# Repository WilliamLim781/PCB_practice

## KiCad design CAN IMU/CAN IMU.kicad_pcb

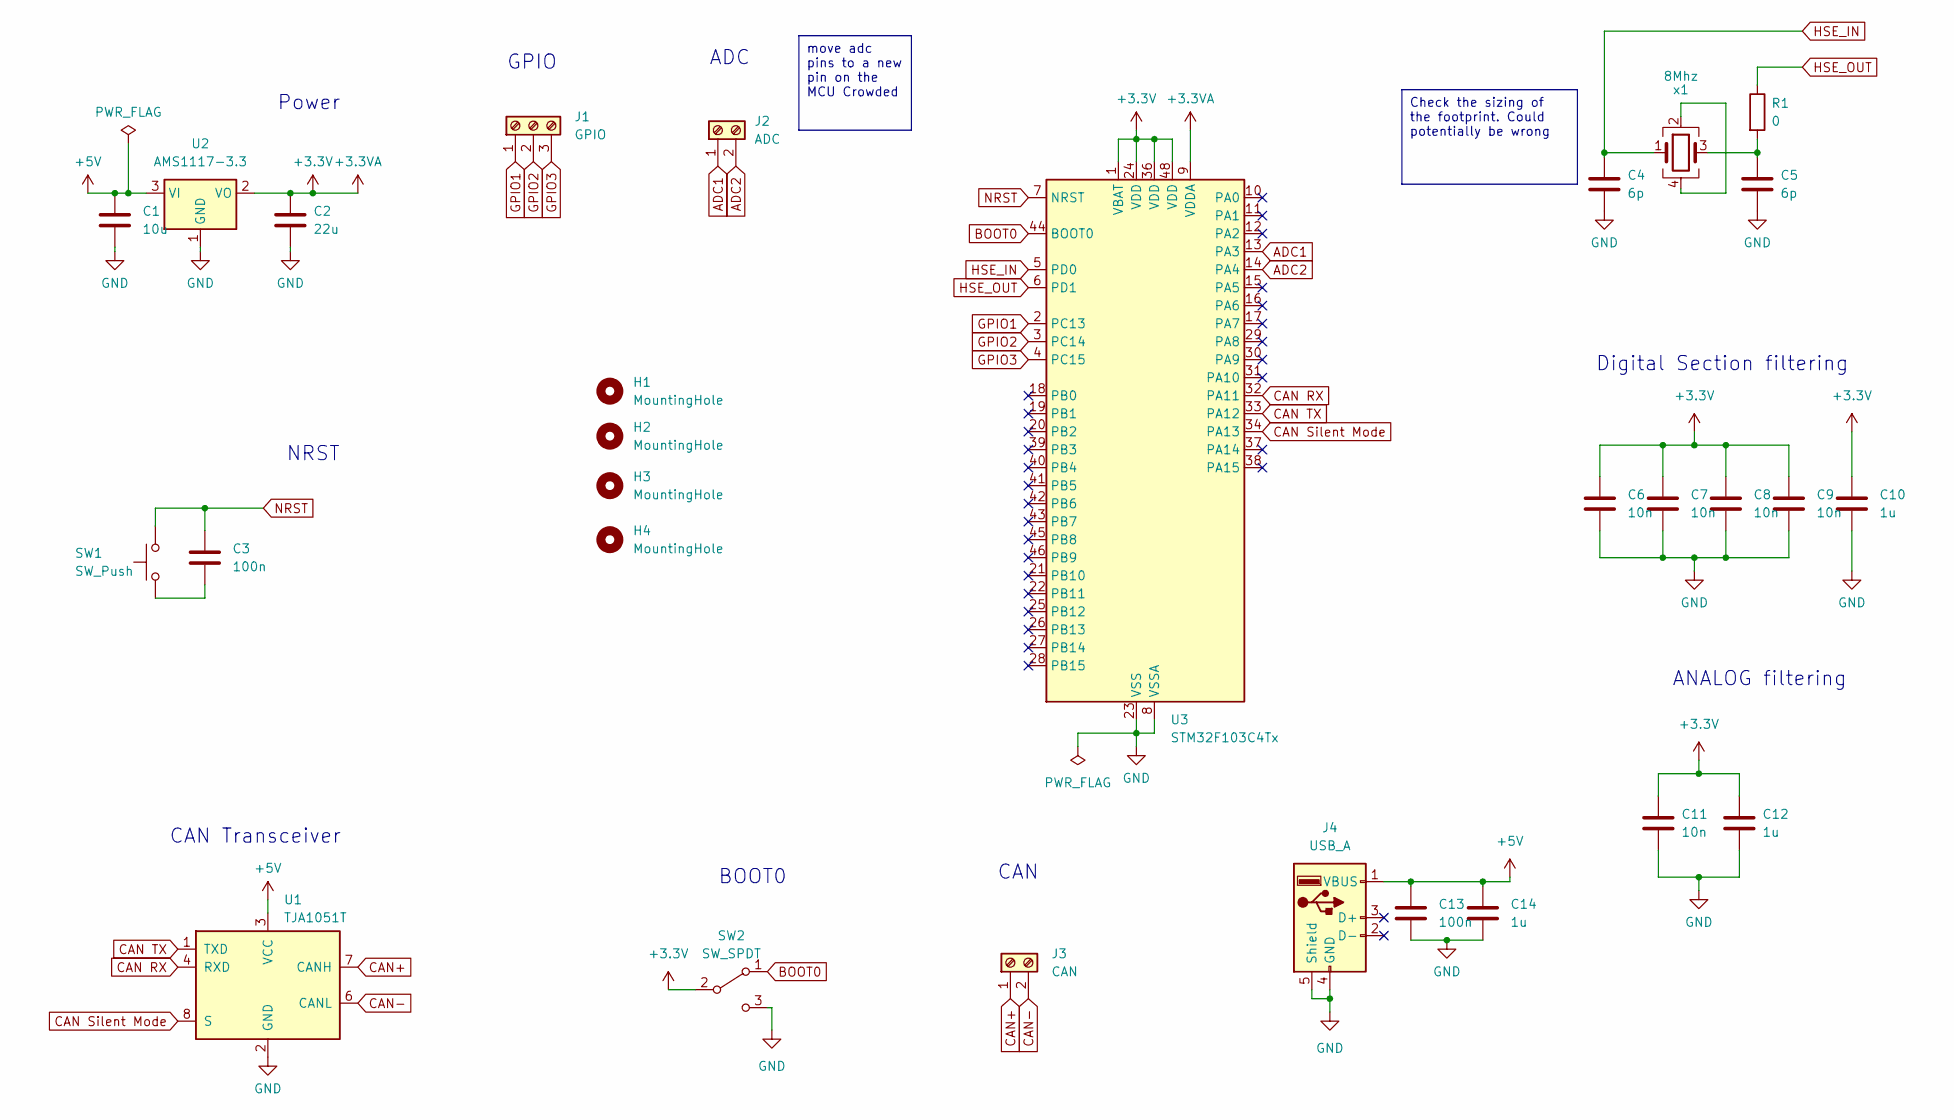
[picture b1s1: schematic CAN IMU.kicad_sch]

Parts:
C1: 10u; C_0603_1608Metric_Pad1.08x0.95mm_HandSolder
C2: 22u; C_0603_1608Metric_Pad1.08x0.95mm_HandSolder
C3, C13: 100n; C_0603_1608Metric_Pad1.08x0.95mm_HandSolder
C4, C5: 6p; C_0603_1608Metric_Pad1.08x0.95mm_HandSolder
C6, C7, C8, C9, C11: 10n; C_0603_1608Metric_Pad1.08x0.95mm_HandSolder
C10, C12, C14: 1u; C_0603_1608Metric_Pad1.08x0.95mm_HandSolder
H1, H2, H3, H4: MountingHole; MountingHole_4.3mm_M4_Pad
J1: GPIO; TerminalBlock_Phoenix_MKDS-1,5-3-5.08_1x03_P5.08mm_Horizont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
J2: ADC; TerminalBlock_Phoenix_MKDS-1,5-2_1x02_P5.00mm_Horizontal
J3: CAN; TerminalBlock_Phoenix_MKDS-1,5-2_1x02_P5.00mm_Horizontal
J4: USB_A; USB_A_Molex_67643_Horizontal
R1: 0; R_0603_1608Metric_Pad0.98x0.95mm_HandSolder
SW1: SW_Push; SW_SPST_PTS645
SW2: SW_SPDT; SW_SPDT_PCM12
U1: TJA1051T; SOIC-8_3.9x4.9mm_P1.27mm
U2: AMS1117-3.3; SOT-223-3_TabPin2
U3: STM32F103C4Tx; LQFP-48_7x7mm_P0.5mm
x1: 8Mhz; Oscillator_SMD_Abracon_ASE-4Pin_3.2x2.5mm_HandSoldering

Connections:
+3.3V: C2.1, C6.1, C7.1, C8.1, C9.1, C10.1, C11.1, C12.1, SW2.2 (B), U2.2 (VO), U3.1 (VBAT), U3.9 (VDDA), U3.24 (VDD), U3.36 (VDD), U3.48 (VDD)
+5V: C1.1, C13.1, C14.1, J4.1 (VBUS), U1.3 (VCC), U2.3 (VI)
ADC1: J2.1, U3.13 (PA3)
ADC2: J2.2, U3.14 (PA4)
BOOT0: SW2.1 (A), U3.44 (BOOT0)
CAN RX: U1.4 (RXD), U3.32 (PA11)
CAN Silent Mode: U1.8 (S), U3.34 (PA13)
CAN TX: U1.1 (TXD), U3.33 (PA12)
CAN+: J3.1, U1.7 (CANH)
CAN-: J3.2, U1.6 (CANL)
GND: C1.2, C2.2, C4.2, C5.2, C6.2, C7.2, C8.2, C9.2, C10.2, C11.2, C12.2, C13.2, C14.2, J4.4 (GND), J4.5 (Shield), SW2.3 (C), U1.2 (GND), U2.1 (GND), U3.8 (VSSA), U3.23 (VSS), U3.35 (VSS), U3.47 (VSS)
GPIO1: J1.1, U3.2 (PC13)
GPIO2: J1.2, U3.3 (PC14)
GPIO3: J1.3, U3.4 (PC15)
HSE_IN: C4.1, U3.5 (PD0), x1.1
HSE_OUT: R1.1, U3.6 (PD1)
NRST: C3.2, SW1.2, U3.7 (NRST)
unnamed: C3.1, SW1.1
unnamed: C5.1, R1.2, x1.3
unnamed: x1.2, x1.4

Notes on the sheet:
Check the sizing of the footprint. Could potentially be wrong
move adc pins to a new pin on the MCU Crowded
CAN Transceiver
Power
NRST
ANALOG filtering
GPIO
BOOT0
ADC
Digital Section filtering
CAN

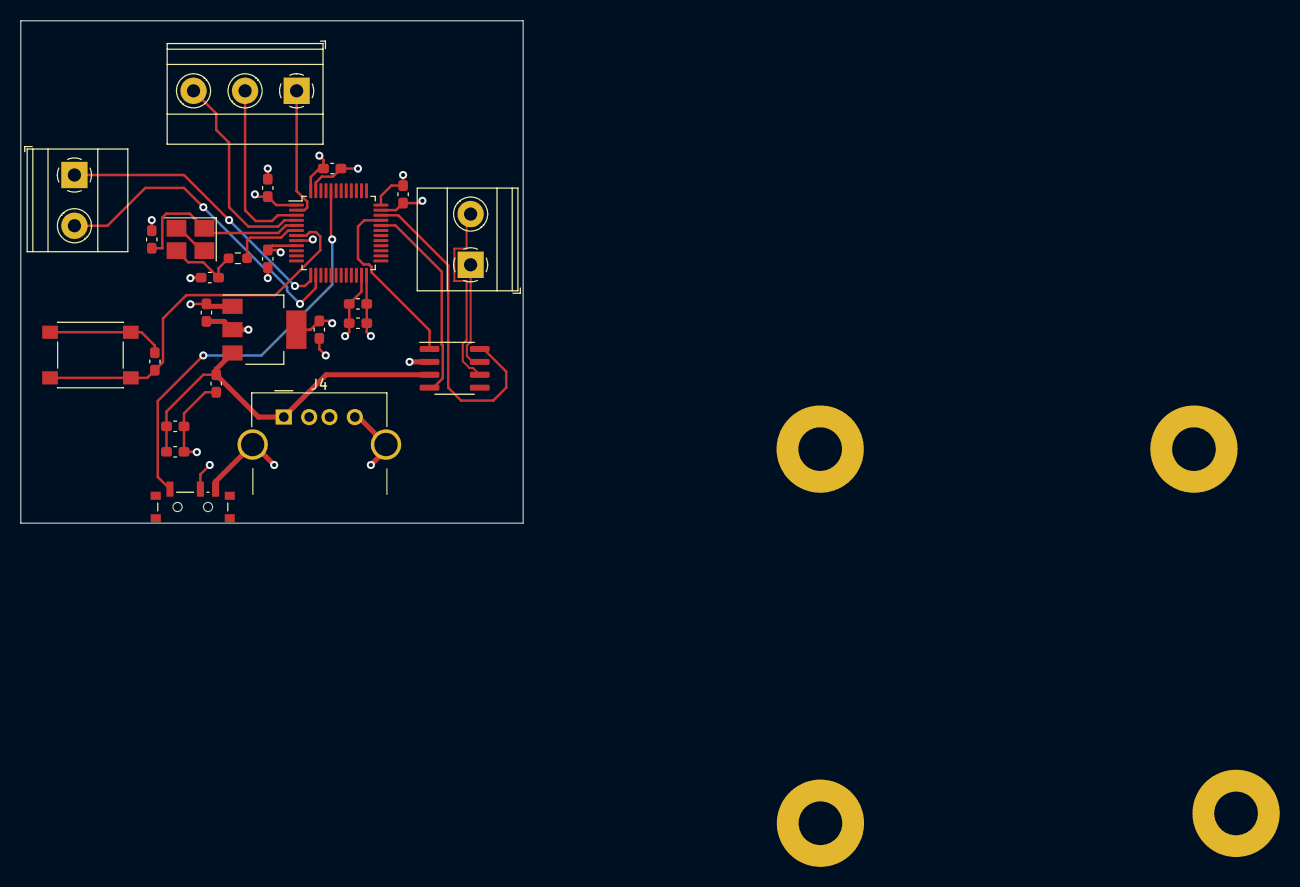
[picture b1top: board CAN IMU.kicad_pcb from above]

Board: 4 copper layers, 49.5 x 49.5 mm, 29 parts (0 on the bottom side), 20 nets.

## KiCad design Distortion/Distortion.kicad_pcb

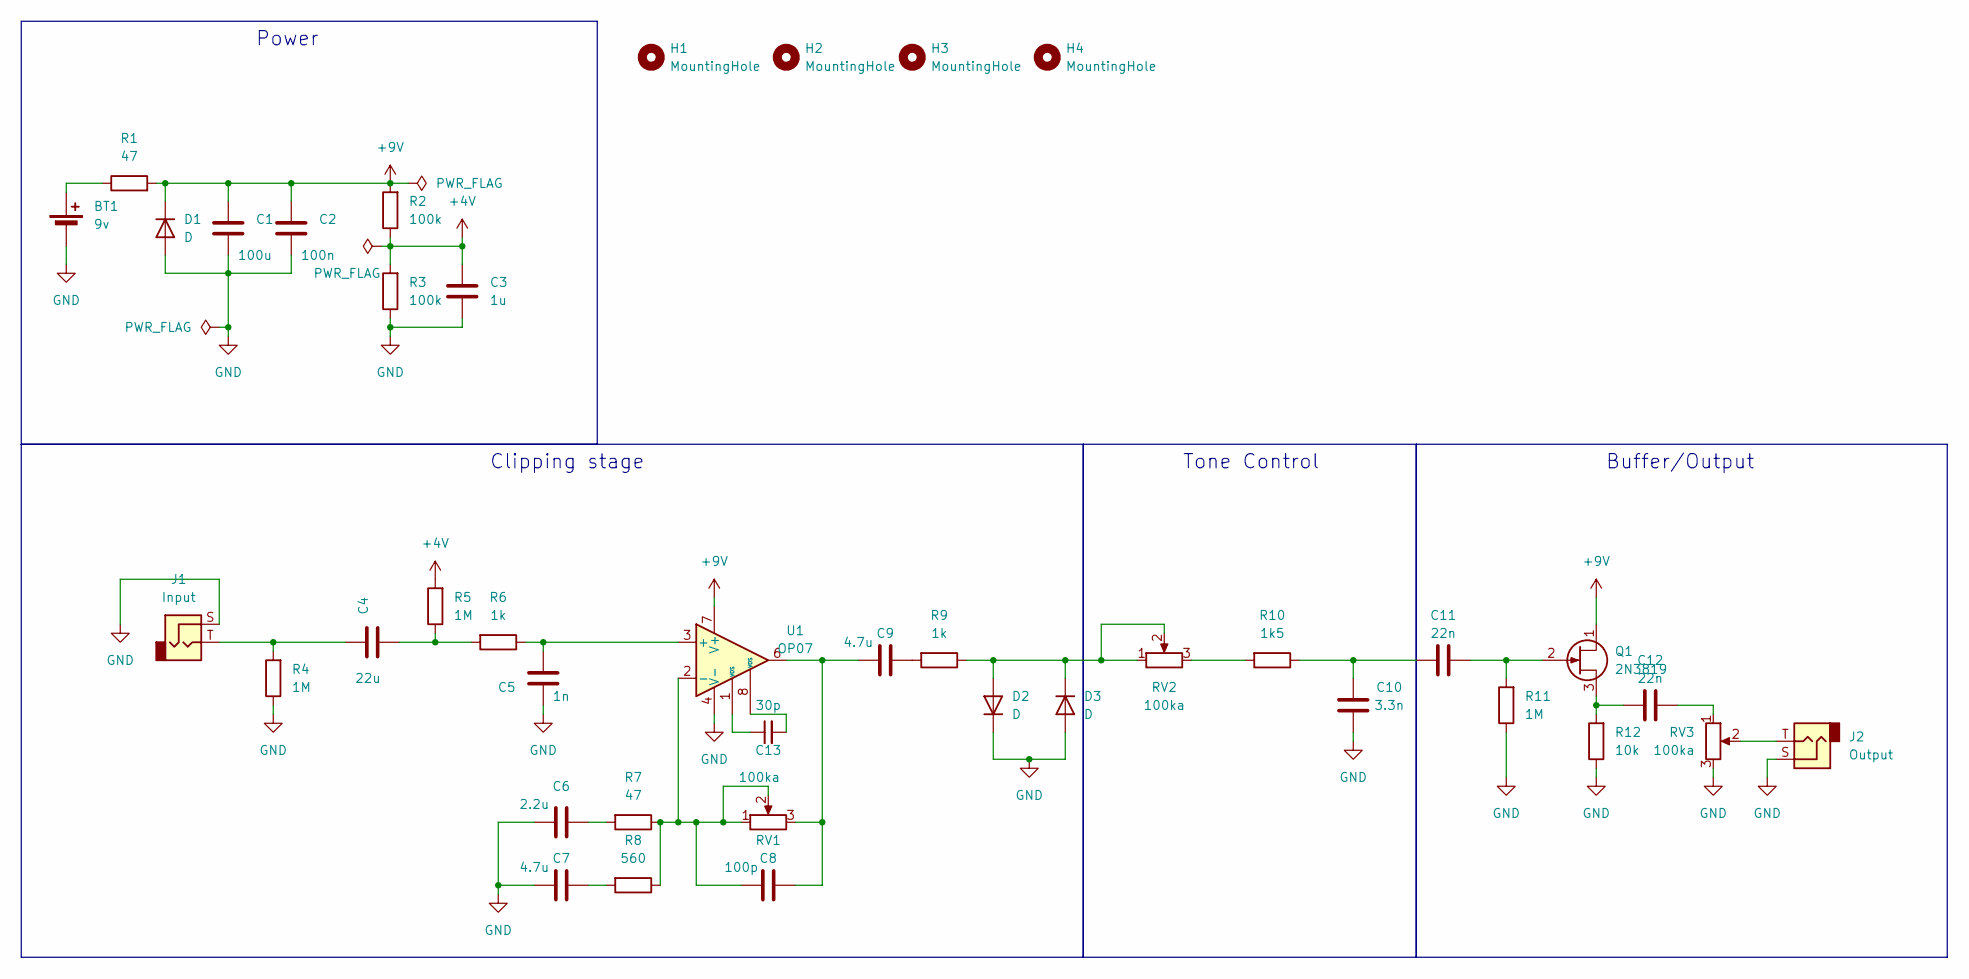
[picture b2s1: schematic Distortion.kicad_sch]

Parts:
BT1: 9v; BatteryHolder_Eagle_12BH611-GR
C1: 100u; C_Disc_D10.5mm_W5.0mm_P10.00mm
C2: 100n; C_Disc_D10.5mm_W5.0mm_P10.00mm
C3: 1u; C_Disc_D10.5mm_W5.0mm_P10.00mm
C4: 22u; C_Disc_D10.5mm_W5.0mm_P10.00mm
C5: 1n; C_Disc_D10.5mm_W5.0mm_P10.00mm
C6: 2.2u; C_Disc_D10.5mm_W5.0mm_P10.00mm
C7, C9: 4.7u; C_Disc_D10.5mm_W5.0mm_P10.00mm
C8: 100p; C_Disc_D10.5mm_W5.0mm_P10.00mm
C10: 3.3n; C_Disc_D10.5mm_W5.0mm_P10.00mm
C11, C12: 22n; C_Disc_D10.5mm_W5.0mm_P10.00mm
C13: 30p; C_Disc_D10.5mm_W5.0mm_P10.00mm
D1, D2, D3: D; D_DO-15_P12.70mm_Horizontal
H1, H2, H3, H4: MountingHole; MountingHole_3.5mm_Pad_Via
J1: Input; Jack_6.35mm_Neutrik_NMJ4HHD2_Horizontal
J2: Output; Jack_6.35mm_Neutrik_NMJ4HHD2_Horizontal
Q1: 2N3819; TO-92
R1, R7: 47; R_Axial_DIN0207_L6.3mm_D2.5mm_P10.16mm_Horizontal
R2, R3: 100k; R_Axial_DIN0207_L6.3mm_D2.5mm_P10.16mm_Horizontal
R4, R5, R11: 1M; R_Axial_DIN0207_L6.3mm_D2.5mm_P10.16mm_Horizontal
R6, R9: 1k; R_Axial_DIN0207_L6.3mm_D2.5mm_P10.16mm_Horizontal
R8: 560; R_Axial_DIN0207_L6.3mm_D2.5mm_P10.16mm_Horizontal
R10: 1k5; R_Axial_DIN0207_L6.3mm_D2.5mm_P10.16mm_Horizontal
R12: 10k; R_Axial_DIN0207_L6.3mm_D2.5mm_P10.16mm_Horizontal
RV1, RV2, RV3: 100ka; Potentiometer_Alps_RK09K_Single_Vertical
U1: OP07; DIP-8_W7.62mm_LongPads

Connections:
+4V: C3.1, R2.1, R3.2, R5.2
+9V: C1.1, C2.1, D1.1 (K), Q1.1 (D), R1.2, R2.2, U1.7 (V+)
GND: BT1.2 (-), C1.2, C2.2, C3.2, C5.1, C6.1, C7.1, C10.1, D1.2 (A), D2.1 (K), D3.2 (A), J1.S, J2.S, R3.1, R4.1, R11.1, R12.1, RV3.3, U1.4 (V-)
unnamed: BT1.1 (+), R1.1
unnamed: C4.1, J1.T, R4.2
unnamed: C4.2, R5.1, R6.2
unnamed: C6.2, R7.2
unnamed: C7.2, R8.2
unnamed: C8.2, C9.1, RV1.3, U1.6
unnamed: C9.2, R9.2
unnamed: C10.2, C11.2, R10.1
unnamed: C12.1, RV3.1
unnamed: C13.1, U1.1 (VOS)
unnamed: C13.2, U1.8 (VOS)
unnamed: D2.2 (A), D3.1 (K), R9.1, RV2.1, RV2.2
unnamed: J2.T, RV3.2
unnamed: C11.1, Q1.2 (G), R11.2
unnamed: C12.2, Q1.3 (S), R12.2
unnamed: R10.2, RV2.3
unnamed: C5.2, R6.1, U1.3 (+)
unnamed: C8.1, R7.1, R8.1, RV1.1, RV1.2, U1.2 (-)

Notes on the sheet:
Power
Tone Control
Clipping stage
Buffer/Output

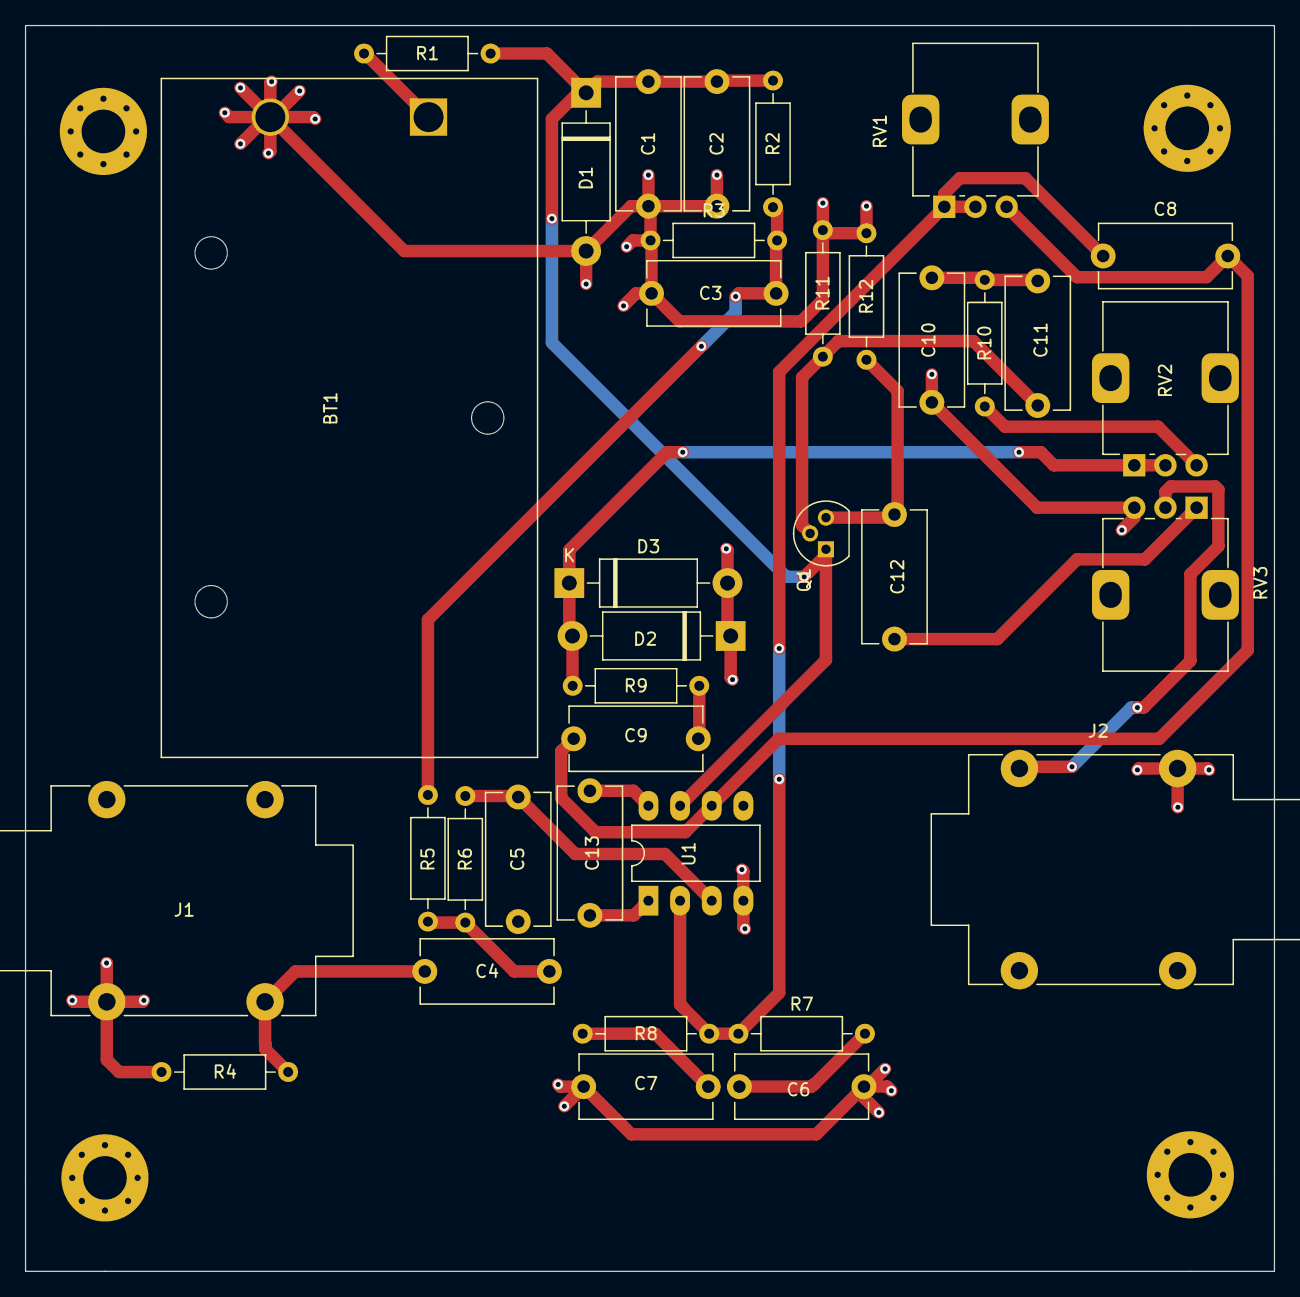
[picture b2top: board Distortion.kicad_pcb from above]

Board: 2 copper layers, 100.2 x 100.0 mm, 40 parts (0 on the bottom side), 21 nets.

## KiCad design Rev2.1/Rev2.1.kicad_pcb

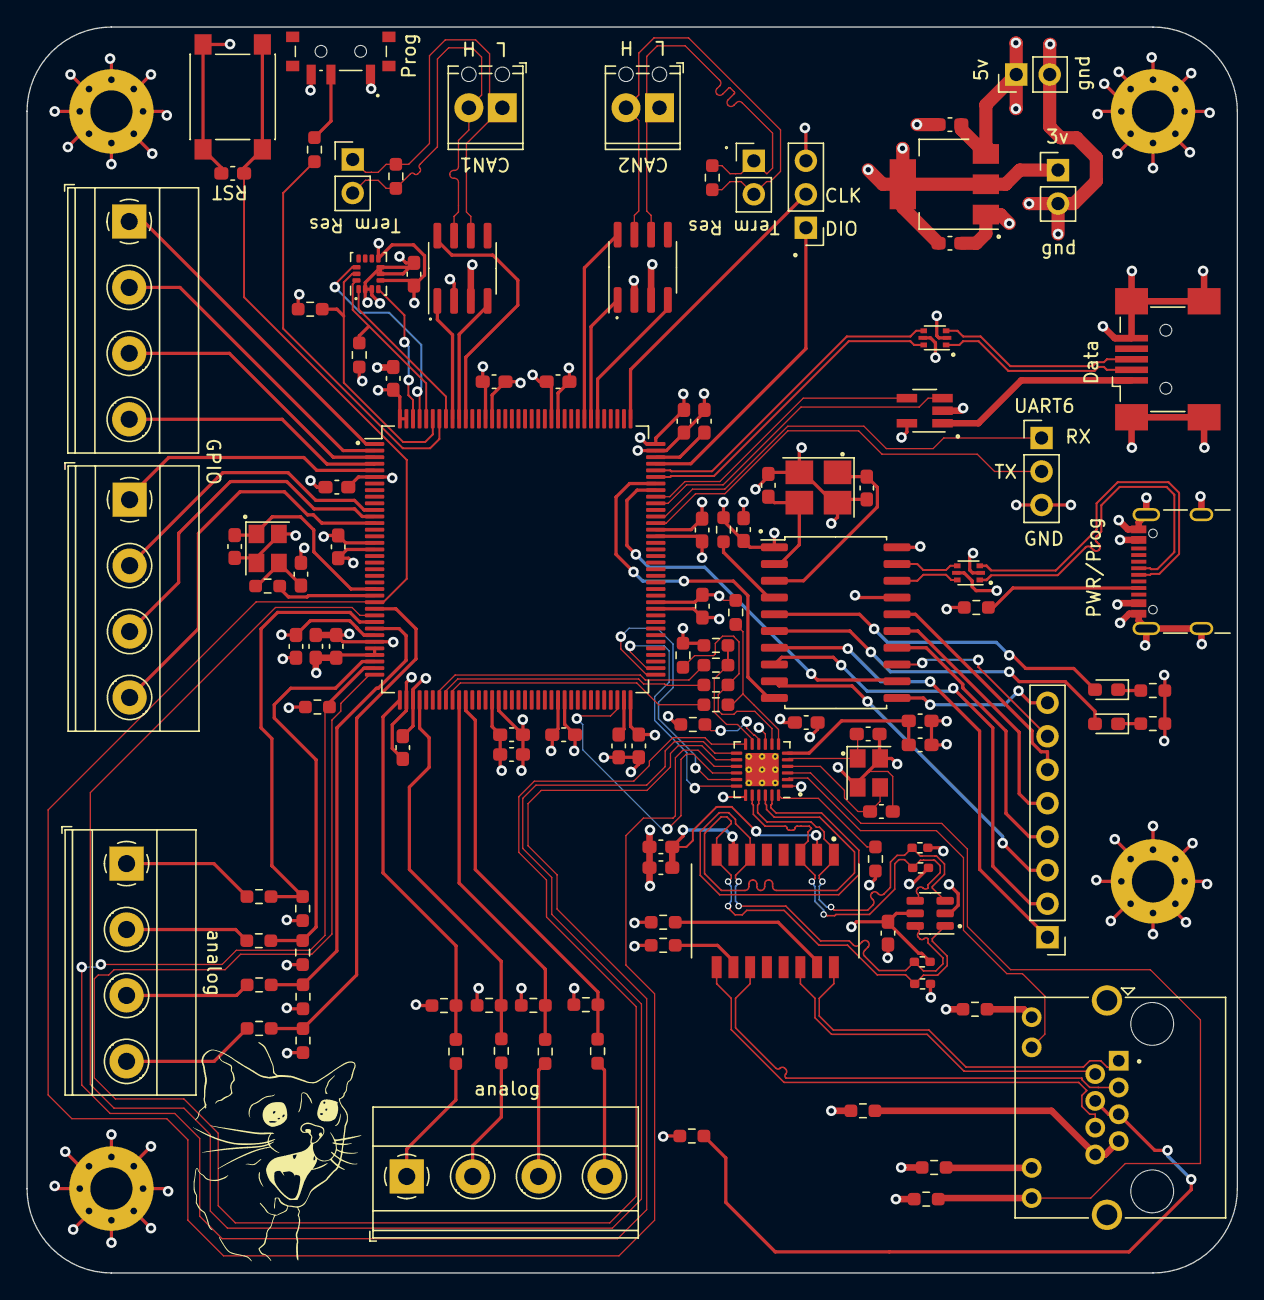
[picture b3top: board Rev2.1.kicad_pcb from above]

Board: 4 copper layers, 91.8 x 94.5 mm, 120 parts (0 on the bottom side), 117 nets.

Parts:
C1, C2, C5, C8, C11, C12, C23, C24, C25, C28, C33, C34, C35, C36, C37, C38, C39, C40, C41, C43, C45: 100n; C_0603_1608Metric_Pad1.08x0.95mm_HandSolder
C3, C4: 6p; C_0603_1608Metric_Pad1.08x0.95mm_HandSolder
C6: 470p; C_0603_1608Metric_Pad1.08x0.95mm_HandSolder
C7, C44: 1u; C_0603_1608Metric_Pad1.08x0.95mm_HandSolder
C9, C10: 22p; C_0603_1608Metric_Pad1.08x0.95mm_HandSolder
C26: 10u; C_0603_1608Metric_Pad1.08x0.95mm_HandSolder
C27, C31: 9p; C_0603_1608Metric_Pad1.08x0.95mm_HandSolder
C29, C30: 2.2u; C_0603_1608Metric_Pad1.08x0.95mm_HandSolder
C32: 22u; C_0603_1608Metric_Pad1.08x0.95mm_HandSolder
C42: 4.7u; C_0603_1608Metric_Pad1.08x0.95mm_HandSolder
D1, D2: LED; LED_0603_1608Metric_Pad1.05x0.95mm_HandSolder
H1, H2, H3, H4: MountingHole_Pad; MountingHole_3.2mm_M3_Pad_Via
J1, J3: Termination; PinHeader_1x02_P2.54mm_Vertical
J2: CAN2; TerminalBlock_Phoenix_MPT-0,5-2-2.54_1x02_P2.54mm_Horizontal
J4: CAN1; TerminalBlock_Phoenix_MPT-0,5-2-2.54_1x02_P2.54mm_Horizontal
J5: SWD; PinHeader_1x03_P2.54mm_Vertical
J6: USB_OTG; USB_Mini-B_Wuerth_65100516121_Horizontal
J7: GPIO1; TerminalBlock_Phoenix_MKDS-1,5-4_1x04_P5.00mm_Horizontal
J8: LIN Pots; TerminalBlock_Phoenix_MKDS-1,5-4_1x04_P5.00mm_Horizontal
J9: AIN; TerminalBlock_Phoenix_MKDS-1,5-4_1x04_P5.00mm_Horizontal
J10: Conn_01x08_Pin; PinHeader_1x08_P2.54mm_Vertical
J11: 3.3V power breakout; PinHeader_1x02_P2.54mm_Vertical
J12: 5V power breakout; PinHeader_1x02_P2.54mm_Vertical
J13: 8P8C_LED; RJ45_Amphenol_RJHSE538X
J14: GPIO2; TerminalBlock_Phoenix_MKDS-1,5-4_1x04_P5.00mm_Horizontal
J15: USART6; PinHeader_1x03_P2.54mm_Vertical
P2: USB_C_Plug_USB2.0; USB_C_Receptacle_GCT_USB4105-xx-A_16P_TopMnt_Horizontal
R1, R2: 120; R_0603_1608Metric_Pad0.98x0.95mm_HandSolder
R3, R9, R10, R11, R12, R13, R14, R15, R16, R36, R37, R39, R40, R41, R42: 10k; R_0603_1608Metric_Pad0.98x0.95mm_HandSolder
R4: 0; R_0603_1608Metric_Pad0.98x0.95mm_HandSolder
R5: 4k7; R_0603_1608Metric_Pad0.98x0.95mm_HandSolder
R6, R7, R45, R46: 2k2; R_0603_1608Metric_Pad0.98x0.95mm_HandSolder
R8: 5k1; R_0603_1608Metric_Pad0.98x0.95mm_HandSolder
R17, R18, R19, R20, R21, R22, R23, R24: 5k6; R_0603_1608Metric_Pad0.98x0.95mm_HandSolder
R25, R26, R27, R28: 75; R_0603_1608Metric_Pad0.98x0.95mm_HandSolder
R29, R30: 270; R_0603_1608Metric_Pad0.98x0.95mm_HandSolder
R31, R32, R33, R34: 50; R_0402_1005Metric_Pad0.72x0.64mm_HandSolder
R35: 12k1; R_0603_1608Metric_Pad0.98x0.95mm_HandSolder
R38, R43, R44: 33; R_0603_1608Metric_Pad0.98x0.95mm_HandSolder
SW3: SW_SPDT; SW_SPDT_PCM12
SW5: SW_Push; SW_SPST_PTS645
T1: H1102NLT; XFMR_H1102NLT
U1: STM32F429ZITx; LQFP-144_20x20mm_P0.5mm
U2, U4: TJA1051T; SOIC-8_3.9x4.9mm_P1.27mm
U3: AMS1117-3.3; SOT-223-3_TabPin2
U5: LGA-14_3x2.5mm_P0.5mm_LayoutBorder3x4y
U6, U10: USBLC6-2P6(ESD protection); SOT-666
U7: MCP2200T-I-SO; SOIC-20W_7.5x12.8mm_P1.27mm
U8: LAN8742A; VQFN-24-1EP_4x4mm_P0.5mm_EP2.5x2.5mm_ThermalVias
U9: STMPS2151STR(Current protection); SOT-23-5_HandSoldering
U12: USBLC6-4SC6; SOT-23-6
Y1: 12MHz; Crystal_SMD_3225-4Pin_3.2x2.5mm_HandSoldering
Y2: 16MHz; Crystal_SMD_3225-4Pin_3.2x2.5mm
Y3: 25Mhz; Crystal_SMD_3225-4Pin_3.2x2.5mm

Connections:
+3.3V: C1.1, C2.1, C5.1, C8.1, C23.1, C24.1, C25.1, C28.1, C32.1, C33.1, C34.1, C35.1, C36.1, C37.1, C38.1, C39.1, C40.1, C41.1, C42.1, C43.1, C44.1, J11.1, R5.2, R31.1, R32.1, R33.1, R34.1, R37.1, R39.1, R40.1, R41.1, R45.1, R46.1, SW3.1 (A), U1.6 (VBAT), U1.17 (VDD), U1.30 (VDD), U1.32 (VREF+), U1.33 (VDDA), U1.39 (VDD), U1.52 (VDD), U1.62 (VDD), U1.72 (VDD), U1.84 (VDD), U1.95 (VDD), U1.108 (VDD), U1.121 (VDD), U1.131 (VDD), U1.143 (PDR_ON), U1.144 (VDD), U3.2 (VO), U5.5 (VDDIO), U5.8 (VDD), U7.1 (VDD), U7.17 (V_USB), U8.1 (VDD2A), U8.9 (VDDIO), U8.19 (VDD1A), U12.5 (VBUS)
+5V: C26.1, J12.1, P2.A4 (VBUS), P2.A9 (VBUS), P2.B4 (VBUS), P2.B9 (VBUS), U2.3 (VCC), U3.3 (VI), U4.3 (VCC), U6.5 (VBUS), U9.5 (VIN), U10.5 (VBUS)
/CAN1+: J3.2, J4.2, R2.2, U4.7 (CANH)
/CAN1-: J3.1, J4.1, R2.1, U4.6 (CANL)
/CAN2+: J1.2, J2.2, R1.2, U2.7 (CANH)
/CAN2-: J1.1, J2.1, R1.1, U2.6 (CANL)
/Ethernet/RX+: R33.2, T1.6, U8.23 (RXP), U12.6 (I/O4)
/Ethernet/RX-: R34.2, T1.8, U8.22 (RXN), U12.1 (I/O1)
/Ethernet/RX->ESD+: J13.3, T1.11
/Ethernet/RX->ESD-: J13.6, T1.9
/Ethernet/TX+: R31.2, T1.1, U8.21 (TXP), U12.3 (I/O2)
/Ethernet/TX-: R32.2, T1.3, U8.20 (TXN), U12.4 (I/O3)
/Ethernet/TX->ESD+: J13.1, T1.16
/Ethernet/TX->ESD-: J13.2, T1.14
/USB wiring/USB->ESD+: P2.A6 (D+), U6.3 (I/O2)
/USB wiring/USB->ESD-: P2.A7 (D-), U6.1 (I/O1)
/USB wiring/VBUS1: J6.1 (VBUS), U9.1 (OUT)
A1: R12.2, R19.1, U1.26 (PC0)
A2: R9.2, R17.1, U1.28 (PC2)
A3: R11.2, R23.1, U1.29 (PC3)
A4: R10.2, R18.1, U1.34 (PA0)
BOOT0: R3.1, U1.138 (BOOT0)
CAN1_RX: U1.114 (PD0), U4.4 (RXD)
CAN1_TX: U1.115 (PD1), U4.1 (TXD)
CAN2_RX: U1.135 (PB5), U2.4 (RXD)
CAN2_TX: U1.136 (PB6), U2.1 (TXD)
CTS: J10.7, U7.13 (CTS)
ETH_CRS_DV: R38.1, U1.43 (PA7)
ETH_MDC: U1.27 (PC1), U8.13 (MDC)
ETH_MDIO: U1.36 (PA2), U8.12 (MDIO)
ETH_REF_CLK: R37.2, U1.35 (PA1), U8.14 (~INT/REFCLKO)
ETH_RXD0: R44.1, U1.44 (PC4)
ETH_RXD1: R43.2, U1.45 (PC5)
ETH_TXD0: U1.73 (PB12), U8.17 (TXD0)
ETH_TXD1: U1.74 (PB13), U8.18 (TXD1)
ETH_TX_EN: U1.70 (PB11), U8.16 (TXEN)
GND: C1.2, C2.2, C3.2, C4.2, C5.2, C6.1, C7.1, C8.2, C9.2, C10.2, C11.2, C12.2, C23.2, C24.2, C25.2, C26.2, C27.2, C28.2, C29.2, C30.2, C31.2, C32.2, C33.2, C34.2, C35.2, C36.2, C37.2, C38.2, C39.2, C40.2, C41.2, C42.2, C43.2, C44.2, C45.2, H1.1, H2.1, H3.1, H4.1, J5.3, J6.5 (GND), J6.6 (Shield), J11.2, J12.2, J15.3, P2.A1 (GND), P2.A12 (GND), P2.S1 (SHIELD), R6.1, R7.1, R8.2, R17.2, R18.2, R19.2, R20.2, R21.2, R22.2, R23.2, R24.2, R25.2, R26.2, R27.2, R28.2, R29.2, R30.2, R35.2, R36.2, R42.1, SW3.3 (C), SW5.1, U1.16 (VSS), U1.31 (VSSA), U1.38 (VSS), U1.51 (VSS), U1.61 (VSS), U1.83 (VSS), U1.94 (VSS), U1.107 (VSS), U1.120 (VSS), U1.130 (VSS), U2.2 (GND), U3.1 (GND), U4.2 (GND), U5.2 (SDX), U5.3 (SCX), U5.6 (GND), U5.7 (GND), U6.2 (GND), U7.20 (VSS), U8.25 (VSS), U9.2 (GND), U10.2 (GND), U12.2 (GND), Y1.2, Y1.4, Y2.2, Y2.4, Y3.2, Y3.4
GP0: J10.6, U7.16 (GP0/SSPND)
GP1: J10.5, U7.15 (GP1/USB-CFG)
GP2: J10.4, U7.14 (GP2)
GP3: J10.3, U7.9 (GP3)
GP4: J10.2, U7.8 (GP4)
GP5: J10.1, U7.7 (GP5)
GPIO1: J7.1, U1.1 (PE2)
GPIO2: J7.2, U1.2 (PE3)
GPIO3: J7.3, U1.3 (PE4)
GPIO4: J7.4, U1.4 (PE5)
GPIO5: J14.1, U1.5 (PE6)
GPIO6: J14.2, U1.11 (PF1)
GPIO7: J14.3, U1.12 (PF2)
GPIO8: J14.4, U1.13 (PF3)
HSE_IN: C27.1, U1.23 (PH0), Y2.1
HSE_OUT: R4.1, U1.24 (PH1)
INTSEL_LED: J13.10, U8.2 (LED2/~INTSEL)
L1: R13.2, R20.1, U1.37 (PA3)
L2: R14.2, R21.1, U1.40 (PA4)
L3: R15.2, R22.1, U1.46 (PB0)
L4: R16.2, R24.1, U1.47 (PB1)
LSM6DSOX_CS: U1.141 (PE0), U5.12 (CS)
LSM6DSOX_SCL: R45.2, U1.139 (PB8), U5.13 (SCL)
LSM6DSOX_SDA: R46.2, U1.140 (PB9), U5.14 (SDA)
LSM6DSOX_SDO: U1.137 (PB7), U5.1 (SD0)
LSM6DSOX_int1: U1.142 (PE1), U5.4 (INT1)
NRST: C45.1, SW5.2, U1.25 (NRST), U8.15 (~RST)
unnamed: C11.1, C12.1, T1.2, T1.7
unnamed: C31.1, R4.2, Y2.3
unnamed: D1.2 (A), U7.6 (GP6/RxLED)
unnamed: D1.1 (K), R6.2
unnamed: D2.2 (A), U7.5 (GP7/TxLED)
unnamed: D2.1 (K), R7.2
unnamed: J8.1, R9.1
unnamed: J8.2, R10.1
unnamed: J8.3, R11.1
unnamed: J8.4, R12.1
unnamed: J9.1, R13.1
unnamed: J9.2, R14.1
unnamed: J9.3, R15.1
unnamed: J9.4, R16.1
unnamed: J13.4, J13.5, R25.1
unnamed: J13.7, J13.8, R28.1
unnamed: J13.9, R29.1
unnamed: J13.11, R30.1
unnamed: P2.A5 (CC), R8.1
unnamed: R26.1, T1.15
unnamed: R27.1, T1.10
unnamed: R3.2, SW3.2 (B)
unnamed: C3.1, U7.2 (OSC1), Y1.3
unnamed: C4.1, U7.3 (OSC2), Y1.1
unnamed: R5.1, U7.4 (RST)
unnamed: R38.2, R41.2, U8.11 (CRS_DV/MODE2)
unnamed: R35.1, U8.24 (RBIAS)
unnamed: R39.2, R44.2, U8.8 (RXD0/MODE0)
unnamed: R40.2, R43.1, U8.7 (RXD1/MODE1)
unnamed: R42.2, U8.10 (RXER/PHYAD0)
unnamed: C6.2, C7.2, U8.6 (VDDCR)
unnamed: C9.1, U8.5 (XTAL1/CLKIN), Y3.1
unnamed: C10.1, U8.4 (XTAL2), Y3.3
REGOFF_LED: J13.12, R36.1, U8.3 (LED1/REGOFF)
RTS: J10.8, U7.11 (RTS)
STMPS2151STR_EN: U1.100 (PA8), U9.4 (EN)
STMPS2151STR_FAULT: U1.99 (PC9), U9.3 (FAULT)
SYS_JTCK_SWCLK: J5.2, U1.109 (PA14)
SYS_JTMS_SWDIO: J5.1, U1.105 (PA13)
Silent_Mode1: U1.116 (PD2), U4.8 (S)
Silent_Mode2: U1.134 (PB4), U2.8 (S)
USART1_RX: U1.102 (PA10), U7.10 (TX)
USART1_TX: U1.101 (PA9), U7.12 (RX)
USART6_RX: J15.1, U1.97 (PC7)
USART6_TX: J15.2, U1.96 (PC6)
USBData->ESD+: J6.3 (D+), U10.3 (I/O2)
USBData->ESD-: J6.2 (D-), U10.1 (I/O1)
USB_DATA+: U1.104 (PA12), U10.4 (I/O2)
USB_DATA-: U1.103 (PA11), U10.6 (I/O1)
USB_PROG+: U6.4 (I/O2), U7.19 (D+)
USB_PROG-: U6.6 (I/O1), U7.18 (D-)
VCAP_1: C29.1, U1.71 (VCAP_1)
VCAP_2: C30.1, U1.106 (VCAP_2)

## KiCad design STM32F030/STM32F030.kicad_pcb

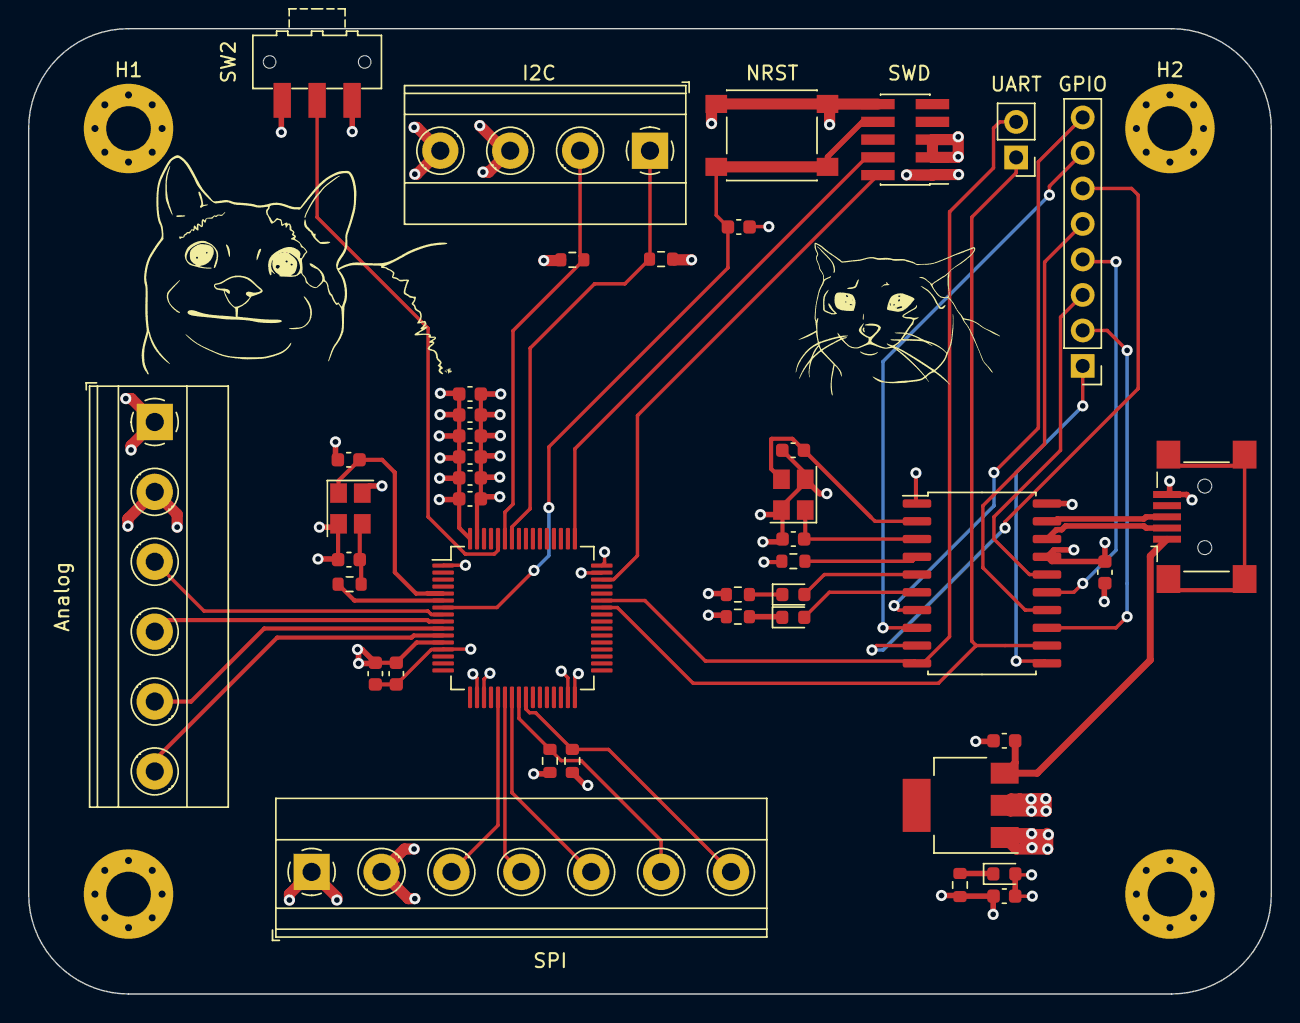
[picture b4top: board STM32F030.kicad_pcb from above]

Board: 4 copper layers, 88.9 x 69.1 mm, 46 parts (0 on the bottom side), 41 nets.

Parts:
Analog: analog pins; TerminalBlock_Phoenix_MKDS-1,5-6_1x06_P5.00mm_Horizontal
C1: 4.7u; C_0603_1608Metric
C2, C3, C4, C5, C6, C12: 100n; C_0603_1608Metric
C7: 10n; C_0603_1608Metric
C8: 1u; C_0603_1608Metric
C9: .1u; C_0603_1608Metric
C10, C11: 9p; C_0603_1608Metric
C13, C14: 6p; C_0603_1608Metric
C15: 10u; C_0603_1608Metric
C16: 22u; C_0603_1608Metric
D1, D2, D3: LED; LED_0603_1608Metric
GPIO: MCP2200 GPIO; PinHeader_1x08_P2.54mm_Vertical
H1, H2, H3, H4: MountingHole; MountingHole_3.2mm_M3_Pad_Via
I2C: I2C; TerminalBlock_Phoenix_MKDS-1,5-4_1x04_P5.00mm_Horizontal
J1: USB_OTG; USB_Mini-B_Lumberg_2486_01_Horizontal
NRST: NRST; SW_SPST_PTS645
R1: 47; R_0603_1608Metric
R2, R6: 10k; R_0603_1608Metric
R3, R4, R5, R7, R9: 2k2; R_0603_1608Metric
R8: 4k7; R_0603_1608Metric
SPI: SPI; TerminalBlock_Phoenix_MKDS-1,5-7_1x07_P5.00mm_Horizontal
SW2: BOOT0; SW_SPDT_CK-JS102011SAQN
SWD: SWD; PinHeader_2x05_P1.27mm_Vertical_SMD
U1: STM32F030RCTx; LQFP-64_10x10mm_P0.5mm
U2: MCP2200T-I-SO; SOIC-20W_7.5x12.8mm_P1.27mm
U3: AZ1117-3.3; SOT-223
UART: UART; PinHeader_1x02_P2.54mm_Vertical
Y1: 16MHz; Crystal_SMD_3225-4Pin_3.2x2.5mm
Y2: 12MHz; Crystal_SMD_3225-4Pin_3.2x2.5mm

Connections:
+3.3V: Analog.2, C1.1, C2.1, C3.1, C4.1, C5.1, C6.1, C7.1, C8.1, C12.1, C16.1, D3.2 (A), I2C.3, R2.1, R4.1, R5.1, R6.1, R8.2, SPI.2, SW2.1 (A), SWD.1, U1.1 (VDD), U1.13 (VDDA), U1.19 (VDD), U1.32 (VDD), U1.48 (VDD), U1.64 (VDD), U2.1 (VDD), U2.17 (V_USB), U3.2 (VO)
+5V: C15.1, J1.1 (VBUS), U3.3 (VI)
Boot0: SW2.2 (B), U1.60 (BOOT0)
CTS: GPIO.2, U2.13 (CTS)
GND: Analog.1, C1.2, C2.2, C3.2, C4.2, C5.2, C6.2, C7.2, C8.2, C9.2, C10.2, C11.2, C12.2, C13.2, C14.2, C15.2, C16.2, I2C.4, J1.5 (GND), NRST.1, R3.1, R7.1, R9.1, SPI.1, SW2.3 (C), SWD.3, SWD.5, SWD.10, U1.12 (VSSA), U1.18 (VSS), U1.31 (VSS), U1.47 (VSS), U1.63 (VSS), U2.20 (VSS), U3.1 (GND), Y1.2, Y1.4, Y2.2, Y2.4
GP0: GPIO.3, U2.16 (GP0/SSPND)
GP1: GPIO.4, U2.15 (GP1/USB-CFG)
GP2: GPIO.5, U2.14 (GP2)
GP3: GPIO.6, U2.9 (GP3)
GP4: GPIO.7, U2.8 (GP4)
GP5: GPIO.8, U2.7 (GP5)
HSE_IN: C10.1, U1.5 (PF0), Y1.1
HSE_OUT: R1.1, U1.6 (PF1)
I2C1_SCL: I2C.1, R4.2, U1.58 (PB6)
I2C1_SDA: I2C.2, R5.2, U1.59 (PB7)
Lin_Pots1: Analog.3, U1.8 (PC0)
Lin_Pots2: Analog.4, U1.9 (PC1)
Lin_Pots3: Analog.5, U1.10 (PC2)
Lin_Pots4: Analog.6, U1.11 (PC3)
NRST: C9.1, NRST.2, SWD.8, U1.7 (NRST)
unnamed: C11.1, R1.2, Y1.3
unnamed: D1.2 (A), U2.6 (GP6/RxLED)
unnamed: D1.1 (K), R3.2
unnamed: D2.2 (A), U2.5 (GP7/TxLED)
unnamed: D2.1 (K), R7.2
unnamed: D3.1 (K), R9.2
unnamed: C14.1, U2.2 (OSC1), Y2.3
unnamed: C13.1, U2.3 (OSC2), Y2.1
unnamed: R8.1, U2.4 (RST)
RTS: GPIO.1, U2.11 (RTS)
SPI1_CS1: R2.2, SPI.6, U1.24 (PC4)
SPI1_CS2: R6.2, SPI.7, U1.25 (PC5)
SPI1_MISO: SPI.4, U1.22 (PA6)
SPI1_MOSI: SPI.5, U1.23 (PA7)
SPI1_SCK: SPI.3, U1.21 (PA5)
SWCLK: SWD.4, U1.49 (PA14)
SWDIO: SWD.2, U1.46 (PA13)
USART1_RX: U1.43 (PA10), U2.10 (TX), UART.2
USART1_TX: U1.42 (PA9), U2.12 (RX), UART.1
USBD+: J1.3 (D+), U2.19 (D+)
USBD-: J1.2 (D-), U2.18 (D-)

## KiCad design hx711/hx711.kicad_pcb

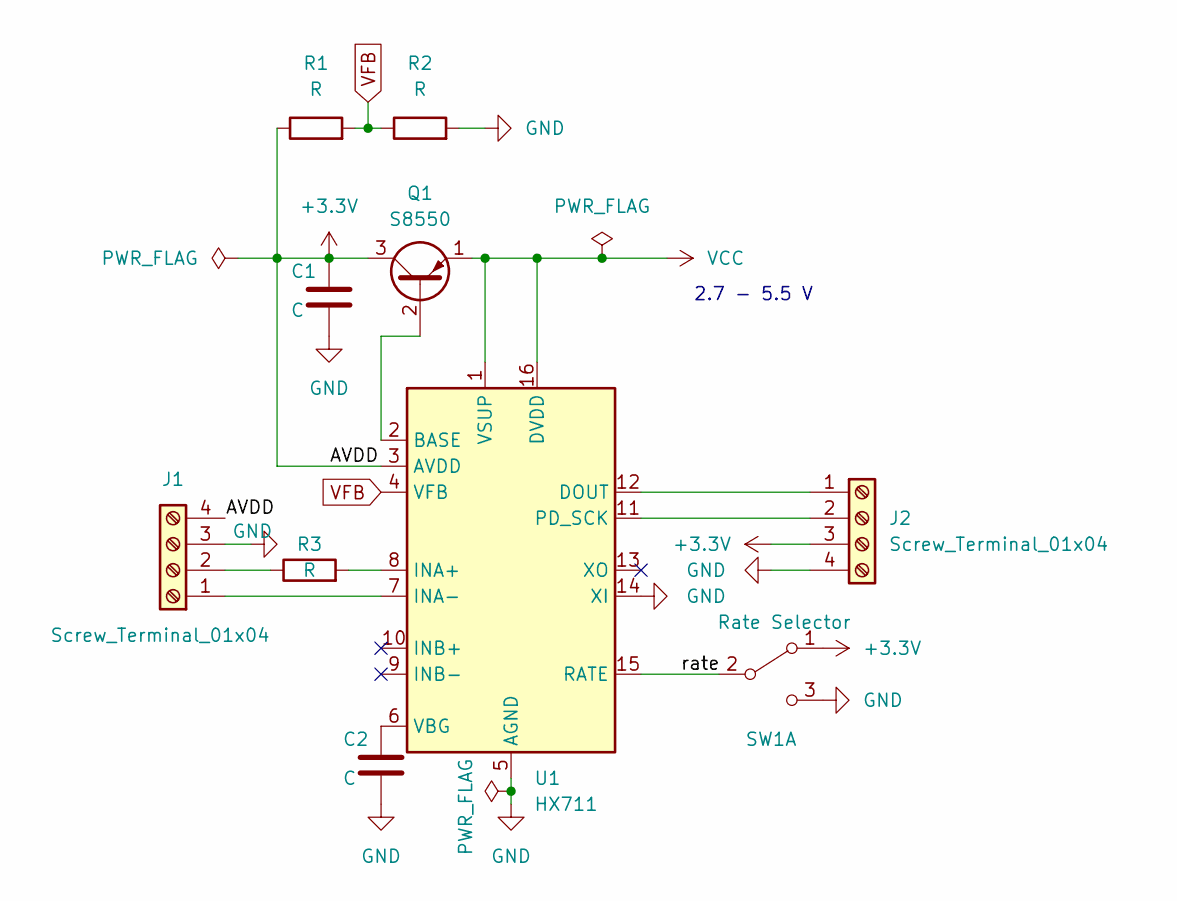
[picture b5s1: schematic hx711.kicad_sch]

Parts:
C1, C2: C; C_0402_1005Metric
J1, J2: Screw_Terminal_01x04; Altech_AK300_1x04_P5.00mm_45-Degree
Q1: S8550; TSOT-23
R1, R2, R3: R; R_0402_1005Metric
SW1: Rate Selector; SW_SPDT_PCM12
U1: HX711; SOP-16_3.9x9.9mm_P1.27mm

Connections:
+3.3V: C1.1, J1.4, J2.3, Q1.3 (C), R1.1, SW1.1 (A), U1.3 (AVDD)
/rate: SW1.2 (B), U1.15 (RATE)
GND: C1.2, C2.2, J1.3, J2.4, R2.2, SW1.3 (C), U1.5 (AGND), U1.14 (XI)
unnamed: J1.1, U1.7 (INA-)
unnamed: J1.2, R3.1
unnamed: J2.1, U1.12 (DOUT)
unnamed: J2.2, U1.11 (PD_SCK)
unnamed: Q1.2 (B), U1.2 (BASE)
unnamed: R3.2, U1.8 (INA+)
unnamed: C2.1, U1.6 (VBG)
VCC: Q1.1 (E), U1.1 (VSUP), U1.16 (DVDD)
VFB: R1.2, R2.1, U1.4 (VFB)

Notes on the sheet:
2.7 - 5.5 V

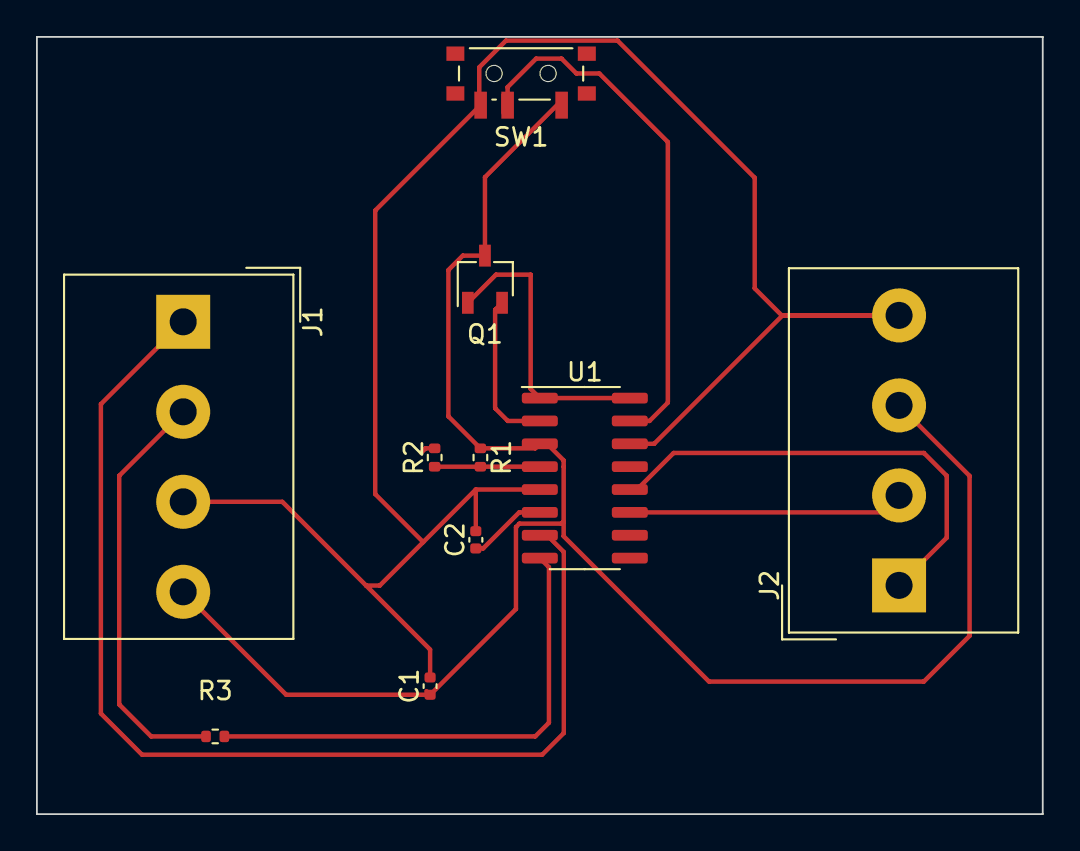
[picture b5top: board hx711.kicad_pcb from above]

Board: 2 copper layers, 55.9 x 43.2 mm, 10 parts (0 on the bottom side), 12 nets.
